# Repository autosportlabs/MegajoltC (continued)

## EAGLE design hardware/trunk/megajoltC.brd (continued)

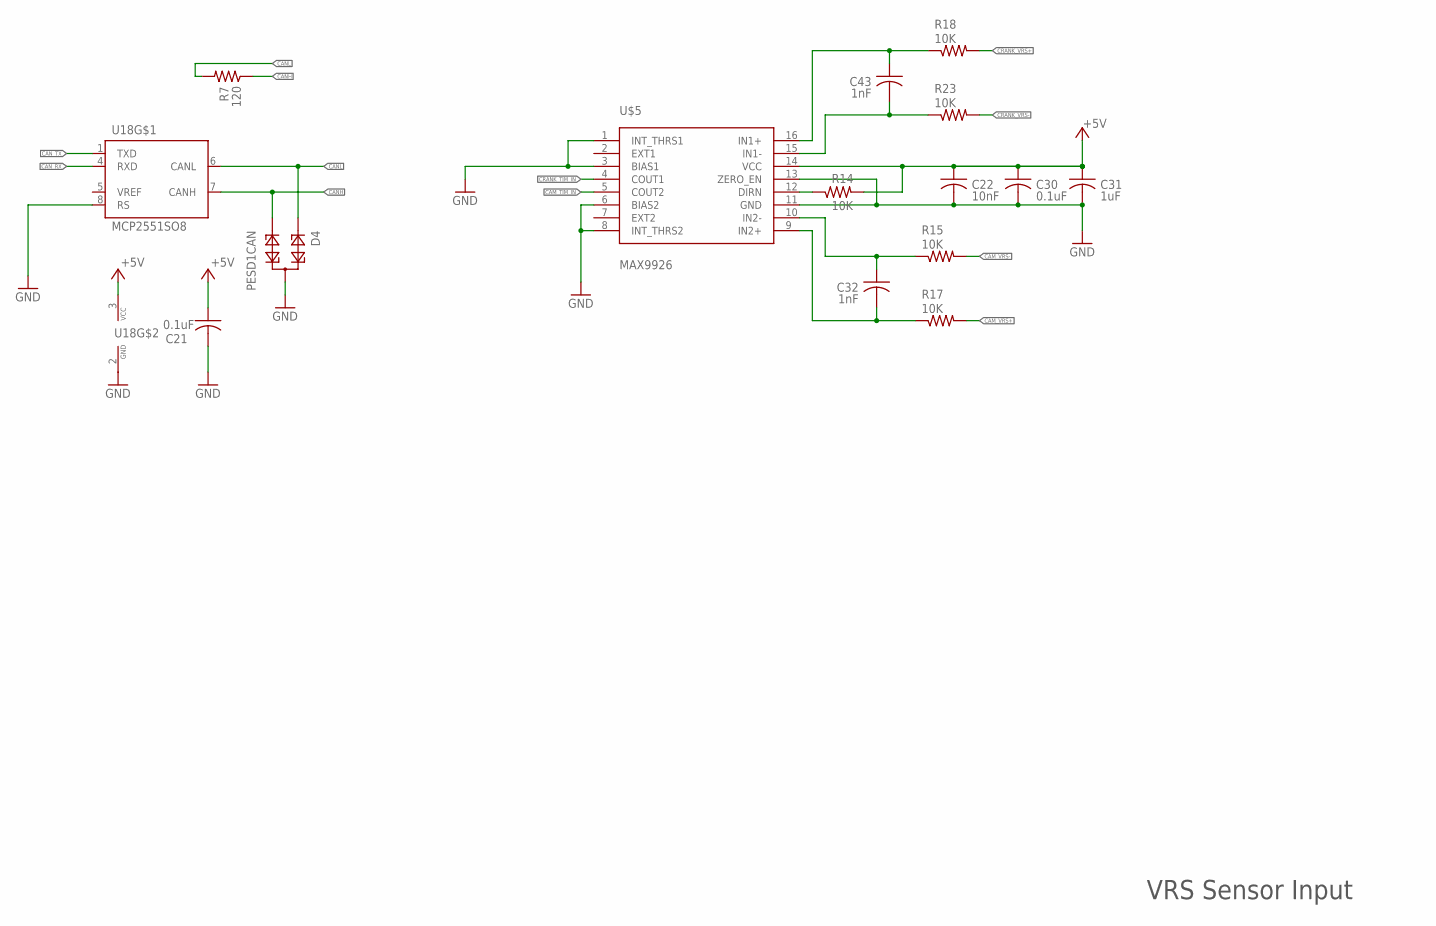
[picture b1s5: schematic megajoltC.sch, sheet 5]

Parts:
C21: 0.1uF; C0603K
C22: 10nF; C0603
C30: 0.1uF; C0603
C31: 1uF; C0603
C32, C43: 1nF; C0603
D4: PESD1CAN; SOT23
R7: 120; R0603
R14, R15, R17, R18, R23: 10K; R0603
U18: MCP2551SO8; SO08
U$5: MAX9926; QSOP16

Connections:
+5V: C21.1, C22.1, C30.1, C31.1, R14.2, U18.3 (VCC), U$5.14 (VCC); also elsewhere on the board
CAM_TIM_IN: U$5.5 (COUT2); also elsewhere on the board
CAM_VRS+: R17.2; also elsewhere on the board
CAM_VRS-: R15.2; also elsewhere on the board
CANH: D4.2, R7.1, U18.7 (CANH); also elsewhere on the board
CANL: D4.1, R7.2, U18.6 (CANL); also elsewhere on the board
CAN_RX: U18.4 (RXD); also elsewhere on the board
CAN_TX: U18.1 (TXD); also elsewhere on the board
CRANK_TIM_IN: U$5.4 (COUT1); also elsewhere on the board
CRANK_VRS+: R18.2; also elsewhere on the board
CRANK_VRS-: R23.2; also elsewhere on the board
GND: C21.2, C22.2, C30.2, C31.2, D4.3, U18.2 (GND), U18.8 (RS), U$5.1 (INT_THRS1), U$5.3 (BIAS1), U$5.6 (BIAS2), U$5.8 (INT_THRS2), U$5.11 (GND), U$5.13 (ZERO_EN); also elsewhere on the board
MAX_DIRN: R14.1, U$5.12 (DIRN)
unnamed: C43.1, R18.1, U$5.16 (IN1+)
unnamed: C32.1, R15.1, U$5.10 (IN2-)
unnamed: C32.2, R17.1, U$5.9 (IN2+)
unnamed: C43.2, R23.1, U$5.15 (IN1-)

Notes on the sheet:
VRS Sensor Input

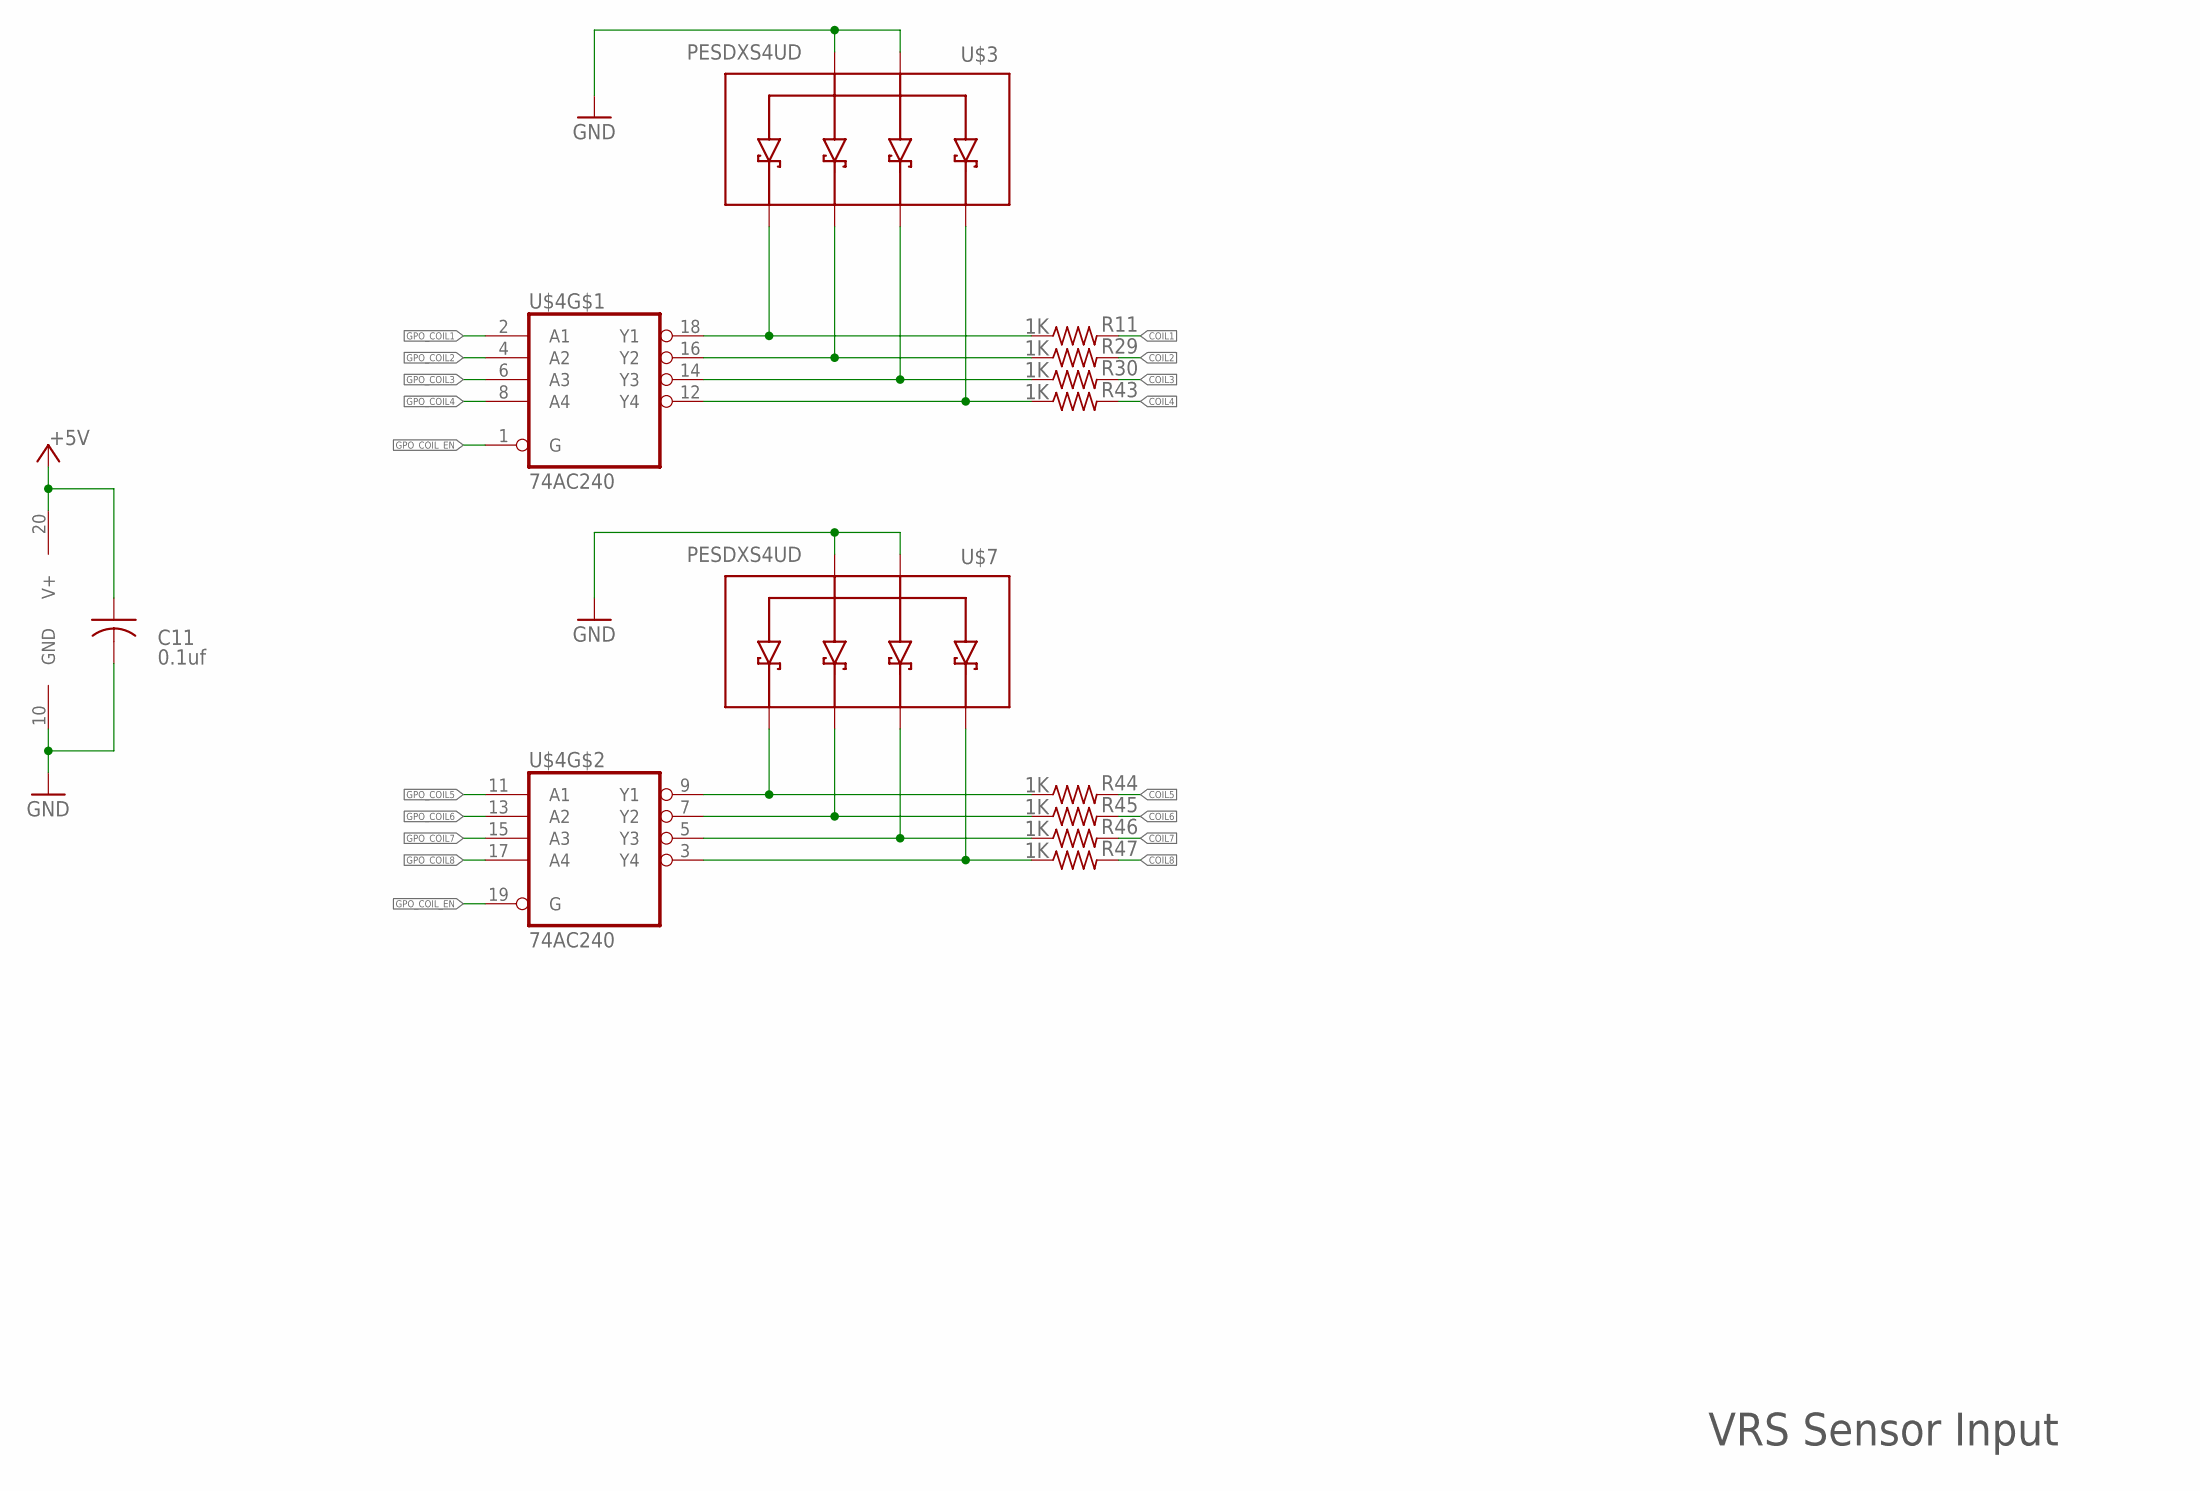
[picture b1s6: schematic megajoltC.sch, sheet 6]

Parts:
C11: 0.1uf; C0603
R11, R29, R30, R43, R44, R45, R46, R47: 1K; R0603
U$3, U$7: PESDXS4UD; SC-74
U$4: 74AC240; TSSOP-20

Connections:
+5V: C11.1, U$4.20 (V+); also elsewhere on the board
COIL1: R11.2; also elsewhere on the board
COIL2: R29.2; also elsewhere on the board
COIL3: R30.2; also elsewhere on the board
COIL4: R43.2; also elsewhere on the board
COIL5: R44.2; also elsewhere on the board
COIL6: R45.2; also elsewhere on the board
COIL7: R46.2; also elsewhere on the board
COIL8: R47.2; also elsewhere on the board
GND: C11.2, U$3.2, U$3.5, U$4.10 (GND), U$7.2, U$7.5; also elsewhere on the board
GPO_COIL1: U$4.2 (A1); also elsewhere on the board
GPO_COIL2: U$4.4 (A2); also elsewhere on the board
GPO_COIL3: U$4.6 (A3); also elsewhere on the board
GPO_COIL4: U$4.8 (A4); also elsewhere on the board
GPO_COIL5: U$4.11 (A1); also elsewhere on the board
GPO_COIL6: U$4.13 (A2); also elsewhere on the board
GPO_COIL7: U$4.15 (A3); also elsewhere on the board
GPO_COIL8: U$4.17 (A4); also elsewhere on the board
GPO_COIL_EN: U$4.1 (G), U$4.19 (G); also elsewhere on the board
unnamed: R11.1, U$3.6, U$4.18 (Y1)
unnamed: R29.1, U$3.4, U$4.16 (Y2)
unnamed: R30.1, U$3.3, U$4.14 (Y3)
unnamed: R43.1, U$3.1, U$4.12 (Y4)
unnamed: R44.1, U$4.9 (Y1), U$7.6
unnamed: R45.1, U$4.7 (Y2), U$7.4
unnamed: R46.1, U$4.5 (Y3), U$7.3
unnamed: R47.1, U$4.3 (Y4), U$7.1

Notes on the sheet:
VRS Sensor Input

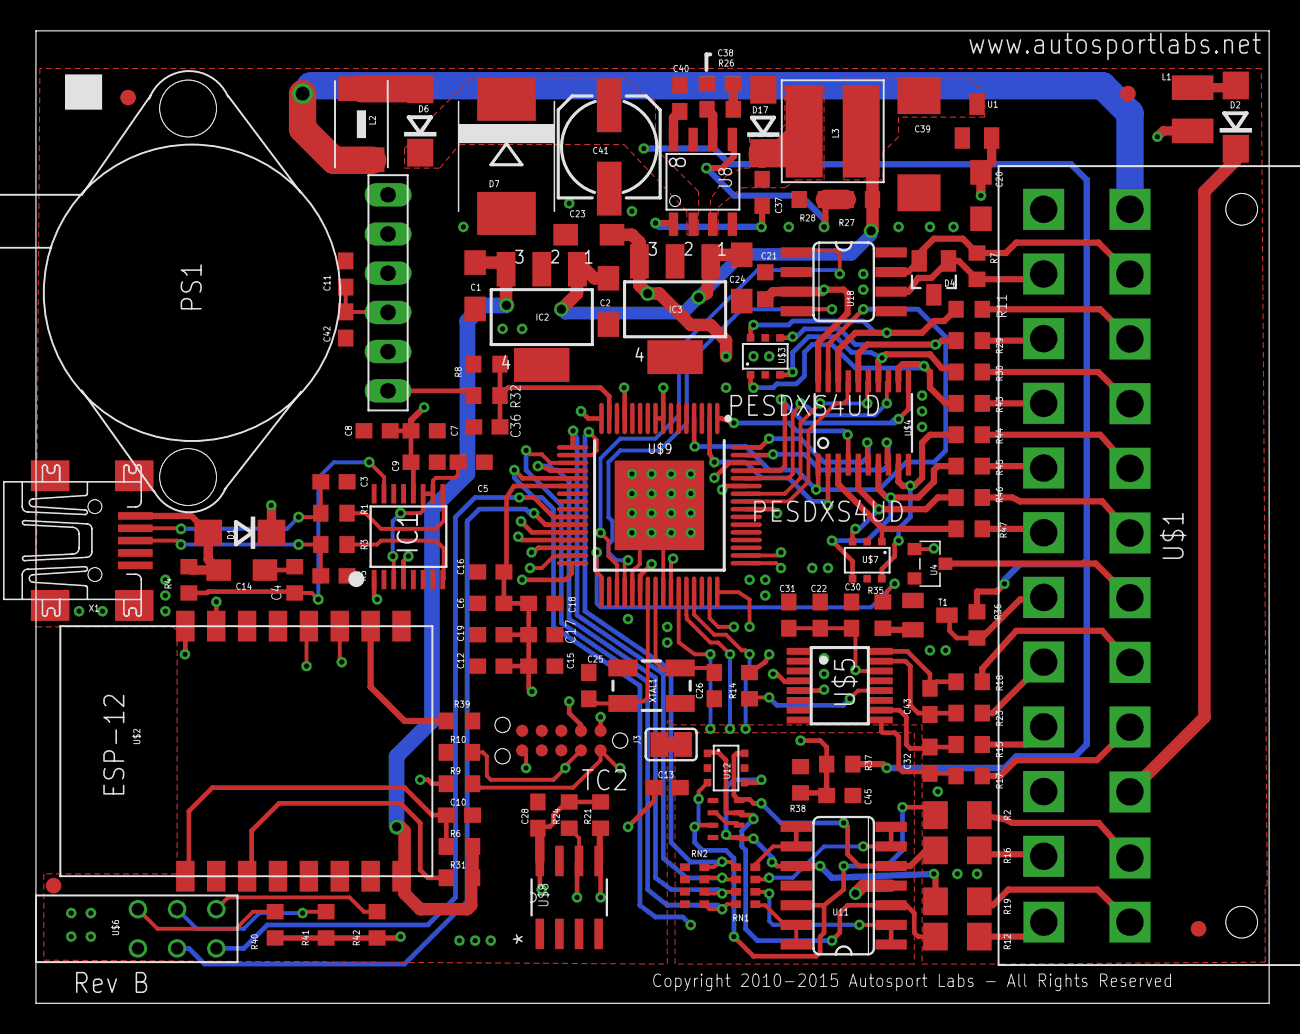
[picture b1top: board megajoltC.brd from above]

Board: 4 copper layers, 79.9 x 63.0 mm, 116 parts (0 on the bottom side), 109 nets.

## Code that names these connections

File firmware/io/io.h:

/*
 * io.h
 *
 *  Created on: Jul 26, 2011
 *      Author: brent
 */
#include <stddef.h>

#ifndef IO_H_
#define IO_H_

#define LED_1 					( 1 << 27 )
#define LED_2 					( 1 << 28 )

#define LED_MASK 				( LED_1 | LED_2 )

#define TACH_OUT 				( 1 << 30 )
#define SHIFT_LIGHT 			( 1 << 20 )
#define PGM_OUT 				( 1 << 11 )
#define OPTION_IN 				( 1 << 26 )

#define BATT_ADC_CHANNEL		0
#define AUX_ADC_CHANNEL			4
#define TPS_ADC_CHANNEL 		5
#define MAP_ADC_CHANNEL			6
#define TEMP_ADC_CHANNEL 		7

#define BATT_ADC				( 1 << BATT_ADC_CHANNEL )
#define AUX_ADC					( 1 << AUX_ADC_CHANNEL )
#define TPS_ADC					( 1 << TPS_ADC_CHANNEL )
#define MAP_ADC					( 1 << MAP_ADC_CHANNEL )
#define TEMP_ADC				( 1 << TEMP_ADC_CHANNEL )

#define ALL_ADC					BATT_ADC | AUX_ADC | TPS_ADC | MAP_ADC | TEMP_ADC

void initIO(void);
void enableLED(unsigned int Led);
void disableLED(unsigned int Led);
void toggleLED (unsigned int Led);
unsigned int readADC(unsigned int channel);
void readAllADC(	unsigned int *a0,
						unsigned int *a1,
						unsigned int *a2,
						unsigned int *a3,
						unsigned int *a4,
						unsigned int *a5,
						unsigned int *a6,
						unsigned int *a7 );

#endif /* IO_H_ */

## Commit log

2010-11-29 initial checkin of megajolt/c hardware
2010-12-05 before adding tach_out and extra ADC
2010-12-05 added tach_out and extra ADC
2010-12-17 updated MegajoltC
2010-12-25 added jtag port, ugh
2011-01-01 RevA final? I think so..
2011-01-08 added smoothing cap to 12v ADC
2011-03-13 RevA1 updates. whew
2011-07-23 hooked in the lua externals project
2011-07-23 added beginning of MegajoltC firmware
2011-07-24 updated for modular firmware
2011-07-24 added base commands file
2011-07-25 added code for compile time inclusion of lua
2011-07-25 removed test command
2011-07-26 update to constants/config mechanism
2011-07-29 brought in CFI code
2011-07-31 updates to firmware, io and so on
2011-07-31 updates to trigger wheel isr
2011-08-30 lots of changes. debugged and fixed edge conditions and so on. good stuff
2011-09-14 added a bunch of api commands
2011-09-26 updates for API, adc calibration
2011-09-26 updates to reflect changes in SAM7s base framework
2011-11-11 updates to make trigger calculation more reliable
2011-11-12 more stability improvments
2011-11-12 figured out instability issue with tooth overrun
2011-11-16 added fixed ignition advance routine and some debug commands
2012-01-02 moved trigger wheel logic out of ISR and into regular code; added LED3; added code to handle disabled trace facility; disabled trace facility'
2012-09-21 removed svn externals file
2012-09-21 moved files
2012-09-21 moved more files
2012-09-21 added submodule SAM7s_base
2012-09-21 fixed makefile to remove reference to base64.c file
2012-09-22 added trigger wheel simulator
2012-09-22 added 2.6 inch dia trigger wheel
2012-09-22 renamed folder
2012-09-22 added signal generator
2012-09-22 moved cad files to new folder
2012-09-22 added submodule for trigger wheel signal generator
2012-09-22 added SAM7s_lua submodule for trigger wheel signal generator
2012-09-22 fixed up makefile to reflect changes in SAM7s_base
2012-09-22 updates to SAM7s_base
2012-09-22 renamed files to make more sense
2012-09-27 updated trigger wheel CAD design
2012-10-09 candidate for Rev B
2012-10-09 rev A release
2012-10-12 updated trigger wheel plate
2012-10-13 updated trigger wheel
2012-10-18 set LED to indicate trigger wheel synchronization
2012-10-18 changed SAM7s_base to SAM7s321_base
2012-10-18 rev b release
2012-10-18 added Rev_B files
2012-10-20 updates to work with SAM7S321
2012-10-20 updated reference for SAM7s_base
2012-10-22 adjusted memory size for SAM7S321
2012-10-22 disabled overriding of heap size
2012-11-11 updated firmware with polling style USB and removed FreeRTOS (for now)
2012-11-12 updates to ignition runtime, extracted FreeRTOS, system initialization
2012-11-12 updated submodule
2013-06-22 removing submodules and simplifying life
2013-06-22 re-added SAM7s base files
2013-06-22 removing folders for now
2013-06-22 added signal generator dependencies
2013-06-22 removed gitmodules file
2013-06-22 removed gitmodules
2013-06-24 added tach out toggling on charge / discharge of coil
2015-01-21 removed SAM7s; cleaned up to prep for XMC; altered power supply and vref circuit
2015-03-21 Schematic V1 for MJ2/C
    Also added pinmux for xmc4200. Board is partially routed to assist in pinout
2015-03-24 Schematic, second draft complete
    Also added gitignore
2015-03-28 Board routed. V1
2015-03-28 Fix minor grounding issue
2015-03-28 Fix DRC Dimension issue
2015-03-29 Change label size on board. Add additional gnd stitching
2015-03-29 Add Fiducial marks
2015-04-11 Slight update to routing
2015-04-11 Remove R13, minor ground pour changes
2015-04-11 Minor layout trace changes
2015-04-11 Fix bad ground path issue
2019-06-10 add readme and license
